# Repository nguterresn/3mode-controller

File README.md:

## **Hardware Controller for Hobbyist Projects with ESPNow, nRF24, and Bluetooth**

This versatile hardware controller is designed to seamlessly integrate with a variety of wireless communication protocols, making it an ideal choice for hobbyist projects, DIY electronics, and prototyping. With support for **ESPNow**, **nRF24**, and **Bluetooth**, this controller offers unparalleled flexibility for creating custom communication setups across different platforms.

### **Key Features:**

- **ESPNow**: Leverage ESP32's ESPNow protocol for fast, low-power, peer-to-peer communication between ESP32 devices. Perfect for IoT projects where devices need to communicate without relying on Wi-Fi or internet connections.
  
- **nRF24**: Incorporates the nRF24 wireless transceiver, enabling reliable and efficient communication for projects using the popular nRF24L01 radio module. Ideal for low-power, long-range wireless setups.

- **Bluetooth**: Equipped with Bluetooth support, allowing wireless connectivity with smartphones, tablets, and other Bluetooth-enabled devices. This makes it perfect for projects that require mobile app interaction or Bluetooth-based control.

- **Versatile Connectivity**: Easily switch between the three wireless protocols based on the requirements of your project, enabling communication over short or long distances, with low or high power consumption.

- **Easy-to-Use Interface**: Simple to interface with microcontrollers like ESP32 or Arduino, with available libraries and example code to get you started quickly.

- **Low Power Consumption**: Designed with power efficiency in mind, making it suitable for battery-powered projects, especially when using ESPNow or nRF24 protocols.

With its easy integration, low power consumption, and flexible wireless communication options, this hardware controller is an essential tool for hobbyists and makers looking to bring their wireless project ideas to life.

### Support

- ✅ ESPNow
- ✅ nRF24
- ❌ Bluetooth (Work in progress)

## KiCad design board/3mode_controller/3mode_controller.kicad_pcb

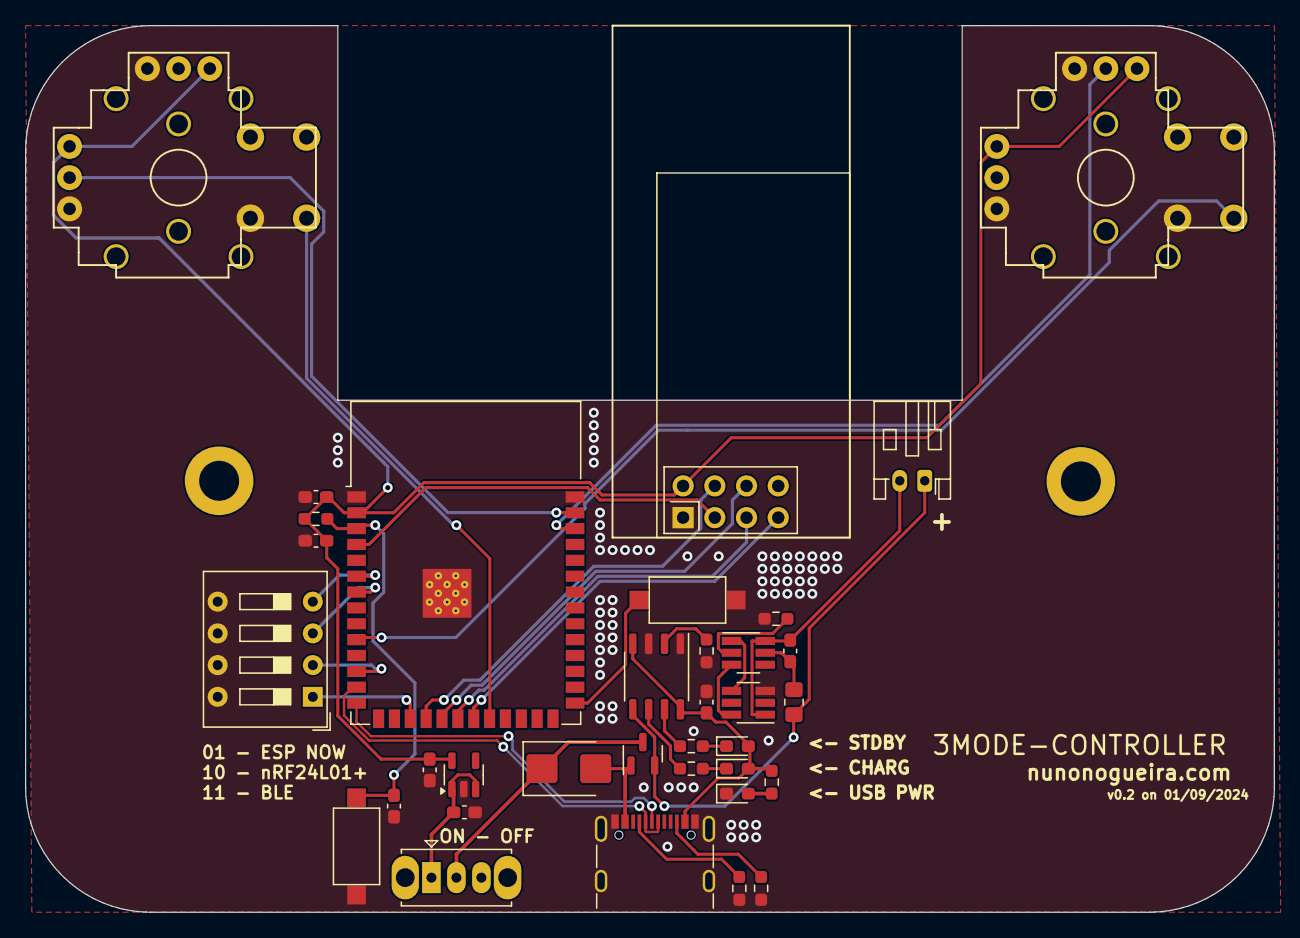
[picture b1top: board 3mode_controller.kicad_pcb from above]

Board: 2 copper layers, 100.0 x 71.0 mm, 37 parts (0 on the bottom side), 36 nets.

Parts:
C1, C6, C9: 1u; C_0603_1608Metric_Pad1.08x0.95mm_HandSolder
C2, C4: 0.1u; C_0603_1608Metric_Pad1.08x0.95mm_HandSolder
C3, C5: 10u; C_0603_1608Metric_Pad1.08x0.95mm_HandSolder
D1: LED; LED_0603_1608Metric_Pad1.05x0.95mm_HandSolder
D2: RLED; LED_0603_1608Metric_Pad1.05x0.95mm_HandSolder
D3: GLED; LED_0603_1608Metric_Pad1.05x0.95mm_HandSolder
D4: VS-10BQ015HM3/5BT; D_SMB
H1, H2: MountingHole; MountingHole_3.2mm_M3_ISO14580_Pad
IC1: DW01A; SOT-23-6_Handsoldering
J1: JST XH; JST_PH_S2B-PH-K_1x02_P2.00mm_Horizontal
J2: USB_C_Receptacle; USB_C_Receptacle_GCT_USB4105-xx-A_16P_TopMnt_Horizontal
Q1: FDN336P; SOT-23
R1, R3, R4, R6, R7, R10: 5.1K; R_0603_1608Metric_Pad0.98x0.95mm_HandSolder
R2: 1.2k; R_0603_1608Metric_Pad0.98x0.95mm_HandSolder
R5: 100; R_0805_2012Metric_Pad1.20x1.40mm_HandSolder
R9: 1k; R_0603_1608Metric_Pad0.98x0.95mm_HandSolder
SW1: reset; SW_SPST_CK_RS282G05A3
SW2: boot; SW_SPST_CK_RS282G05A3
SW3: SW_DIP_x04; SW_DIP_SPSTx04_Slide_9.78x12.34mm_W7.62mm_P2.54mm
SW4: SW_SPDT; SW_Slide_1P2T_CK_OS102011MS2Q
U1: TP4056; SOP-8_3.9x4.9mm_P1.27mm
U2: ESP32-S3-WROOM-1
U3: AP2112K-3.3; SOT-23-5
U4: FH8205; SOT-23-6_Handsoldering
U6: NRF24L01_Breakout; nRF24L01_Breakout
U7, U8: RKJXV1224005

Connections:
+3.3V: C3.1, C5.1, C9.1, R1.1, U2.2 (3V3), U3.5 (VOUT), U6.2 (VCC), U7.1 (LR1), U7.4 (UD1), U8.1 (LR1), U8.4 (UD1)
+5V: C2.1, D2.2 (A), D3.2 (A), D4.2 (A), J2.A4 (VBUS), J2.A9 (VBUS), J2.B4 (VBUS), J2.B9 (VBUS), Q1.1 (G), R7.2, U1.4 (VCC), U1.8 (CE)
ESP32-BOOT0: SW2.1, U2.27 (GPIO0/BOOT)
ESP32-D+: J2.A6 (D+), J2.B6 (D+), U2.14 (GPIO20/U1CTS/ADC2_CH9/CLK_OUT1/USB_D+)
ESP32-D-: J2.A7 (D-), J2.B7 (D-), U2.13 (GPIO19/U1RTS/ADC2_CH8/CLK_OUT2/USB_D-)
ESP32-PULLUP-1: SW3.4, U2.6 (GPIO6/TOUCH6/ADC1_CH5)
ESP32-PULLUP-2: SW3.3, U2.7 (GPIO7/TOUCH7/ADC1_CH6)
ESP32-PULLUP-3: SW3.2, U2.12 (GPIO8/TOUCH8/ADC1_CH7/SUBSPICS1)
ESP32-PULLUP-4: SW3.1, U2.17 (GPIO9/TOUCH9/ADC1_CH8/FSPIHD/SUBSPIHD)
ESP32-RESET: C1.1, R1.2, SW1.1, U2.3 (EN)
ESP32_JOYSTICK_X: U2.38 (GPIO2/TOUCH2/ADC1_CH1), U8.2 (LR2)
ESP32_JOYSTICK_Y: U2.39 (GPIO1/TOUCH1/ADC1_CH0), U7.5 (UD2)
ESP32_RF_SPI_CE: U2.4 (GPIO4/TOUCH4/ADC1_CH3), U6.3 (CE)
ESP32_RF_SPI_CNS: U2.18 (GPIO10/TOUCH10/ADC1_CH9/FSPICS0/FSPIIO4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), U6.4 (~CSN)
ESP32_RF_SPI_MISO: U2.21 (GPIO13/TOUCH13/ADC2_CH2/FSPIQ/FSPIIO7/S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), U6.7 (MISO)
ESP32_RF_SPI_MOSI: U2.19 (GPIO11/TOUCH11/ADC2_CH0/FSPID/FSPIIO5/S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), U6.6 (MOSI)
ESP32_RF_SPI_SCK: U2.20 (GPIO12/TOUCH12/ADC2_CH1/FSPICLK/FSPIIO6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), U6.5 (SCK)
GND: C1.2, C2.2, C3.2, C5.2, C6.2, C9.2, D1.1 (K), J2.A1 (GND), J2.A12 (GND), J2.B1 (GND), J2.B12 (GND), J2.S1 (SHIELD), R2.2, R3.1, R4.2, R9.1, SW1.2, SW2.2, SW3.5, SW3.6, SW3.7, SW3.8, U1.1 (TEMP), U1.3 (GND), U2.1 (GND), U2.40 (GND), U2.41 (GND), U3.2 (GND), U4.3 (S2), U6.1 (GND), U7.3 (LR3), U7.6 (UD3), U7.7 (SWa), U8.3 (LR3), U8.6 (UD3), U8.7 (SWa)
JS_LEFT_IRQ: U2.22 (GPIO14/TOUCH14/ADC2_CH3/FSPIWP/FSPIDQS/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), U7.8 (SWb)
JS_RIGHT_IRQ: U2.10 (GPIO17/U1TXD/ADC2_CH6), U8.8 (SWb)
unnamed: D1.2 (A), R7.1
unnamed: D2.1 (K), R10.1
unnamed: D3.1 (K), R6.1
unnamed: IC1.2 (CS), R9.2
unnamed: C4.2, IC1.6 (GND), J1.2, U4.1 (S1)
unnamed: IC1.3 (OC), U4.6 (G2)
unnamed: IC1.1 (OD), U4.4 (G1)
unnamed: C4.1, IC1.5 (VCC), R5.2
unnamed: J2.A5 (CC1), R3.2
unnamed: J2.B5 (CC2), R4.1
unnamed: C6.1, SW4.1 (A), U3.1 (VIN), U3.3 (EN)
unnamed: R2.1, U1.2 (PROG)
unnamed: R10.2, U1.7 (~CHRG)
unnamed: R6.2, U1.6 (~STDBY)
VBAT+PROTECT: J1.1, Q1.2 (S), R5.1, U1.5 (BAT)
VSPLY: D4.1 (K), Q1.3 (D), SW4.2 (B)

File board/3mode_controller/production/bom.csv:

Designator,Footprint,Quantity,Value,LCSC Part #
"C1, C6, C9",0603,3,1u,C1592
"C2, C4",0603,2,0.1u,C30926
"C3, C5",0603,2,10u,C380316
D1,0603,1,LED,C965799
D2,0603,1,RLED,
D3,0603,1,GLED,
D4,D_SMB,1,VS-10BQ015HM3/5BT,C413465
"H1, H2",MountingHole_3.2mm_M3_ISO14580_Pad,2,MountingHole,
IC1,SOT-23-6_Handsoldering,1,DW01A,C351410
J1,JST_PH_S2B-PH-K_1x02_P2.00mm_Horizontal,1,JST XH,C722769
J2,USB_C_Receptacle_GCT_USB4105-xx-A_16P_TopMnt_Horizontal,1,USB_C_Receptacle,C2765186
Q1,SOT-23,1,FDN336P,C19188376
"R1, R10, R3, R4, R6, R7",0603,6,5.1K,C2907114
R2,0603,1,1.2k,C118396
R5,0805,1,100,C17408
R9,0603,1,1k,C328340
SW1,SW_SPST_CK_RS282G05A3,1,reset,
SW2,SW_SPST_CK_RS282G05A3,1,boot,
SW3,SW_DIP_SPSTx04_Slide_9.78x12.34mm_W7.62mm_P2.54mm,1,SW_DIP_x04,C25503179
SW4,SW_Slide_1P2T_CK_OS102011MS2Q,1,SW_SPDT,C431548
U1,SOP-8_3.9x4.9mm_P1.27mm,1,TP4056,C16581
U2,ESP32-S3-WROOM-1,1,ESP32-S3-WROOM-1,C2913198
U3,SOT-23-5,1,AP2112K-3.3,C51118
U4,SOT-23-6_Handsoldering,1,FH8205,C2928988
U6,nRF24L01_Breakout,1,NRF24L01_Breakout,
"U7, U8",RKJXV1224005,2,RKJXV1224005,C918854

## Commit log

2024-04-20 some changes here and there
2024-04-20 prevent race conditions
2024-04-20 rf app
2024-04-21 added ble init and deinit
2024-04-21 started working on the schematic
2024-04-21 schematic finished
2024-04-21 New pins for esp32s3
2024-04-21 moved gitignore aroung
2024-04-21 added the joysticks to the schematic
2024-04-21 added symbols and footprints for the battery charging ICs
2024-04-21 first pcb version
2024-04-21 updated one missing footprint
2024-08-04 first prototype board
2024-08-25 a lot of changes but still a work in progress !
2024-08-25 esp now should be working now!
2024-08-25 a few changes
2024-09-01 support for nrf24l01+
2024-09-02 v0.2.
    Replaced diode and LDO
2024-09-07 naming
2024-09-07 format
